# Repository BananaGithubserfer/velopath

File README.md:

# VeloPath

VeloPath is a multi-part cycling navigation project that combines a mobile application, embedded firmware, electronics design, and engineering documentation in one repository.

The repository contains:

- an Android application with map-based routing and BLE integration
- STM32 firmware for the handlebar module
- ESP-based firmware experiments and tools
- PCB design files and production artifacts
- project documentation, reports, and presentation materials

## Project Overview

VeloPath is organized as a single workspace for both software and hardware development. The Android app is responsible for route search, map display, navigation flow, and communication with the handlebar device. The embedded side includes STM32 firmware for the main hardware module and a separate ESP area for related experiments and peripherals.

At the application level, the current Android project includes:

- destination search and map interaction
- route building and route analytics
- BLE device diagnostics
- handlebar communication for navigation cues
- user settings such as theme and rider speed

## Repository Structure

```text
velopath/
|- app/
|  `- velopath3_project/    Android app and canonical STM32 firmware
|- firmware/
|  `- esp/                  ESP code and isolated tools
|- pcb/                     KiCad projects and manufacturing outputs
|- documentation/           Reports, engineering docs, mechanical docs
|- advertising/             Brochures, presentations, visual assets
|- INDEX.md                 Detailed project map
`- START_HERE.md            Quick onboarding guide
```

## Main Components

### Android App

Path: `app/velopath3_project`

Stack:

- Kotlin
- Jetpack Compose
- Android Navigation Compose
- Yandex MapKit
- Google Play Services Location

The main navigation flow currently includes:

- `DashboardScreen` for search and quick route entry
- `RideMapScreen` for active route guidance and map view
- `DeviceDiagnosticsScreen` for BLE connection and device checks
- `SettingsScreen` for app preferences

### STM32 Firmware

Path: `app/velopath3_project/firmware`

This area contains firmware for the handlebar module based on `STM32F103RGTx`. The documented hardware integration includes:

- BLE UART bridge `WH-BLE106`
- compass `LIS3MDL`
- left and right vibration channels

The firmware tree includes CubeMX project files, startup code, drivers, linker scripts, and diagnostics tooling.

### ESP Area

Path: `firmware/esp`

This directory is the isolated zone for ESP-related source code and tools. Build output and temporary files are local-only and ignored.

### PCB and Electronics

Path: `pcb`

This directory contains KiCad schematics, PCB layouts, fabrication outputs, and related electronics assets.

### Documentation and Materials

Paths:

- `documentation`
- `advertising`

These directories hold project reports, engineering notes, explanatory materials, brochures, and visual assets.

## Quick Start

### 1. Explore the Repository

Start here if you are new to the project:

1. Open `START_HERE.md`
2. Read `INDEX.md`
3. Review `documentation/software_stack_non_esp.md`

### 2. Build the Android App

Run in `app/velopath3_project`:

```powershell
.\gradlew.bat :app:assembleDebug
```

Release build:

```powershell
.\gradlew.bat :app:assembleRelease
```

The Android project expects local configuration through standard Gradle local files in the project root.

### 3. Work with STM32 Firmware

Start in `app/velopath3_project/firmware` if you are working on the main handlebar firmware. Typical files include:

- `firmware.ioc`
- `Core/`
- `Drivers/`
- `Startup/`
- STM32 linker scripts

### 4. Work with ESP Firmware

For ESP tasks, use `firmware/esp`.

Example PlatformIO upload command from the ESP project root:

```powershell
python -m platformio run -t upload --upload-port COM5
```

## Important Project Documents

- `START_HERE.md` - onboarding order for new contributors
- `INDEX.md` - high-level project map
- `documentation/software_stack_non_esp.md` - software overview outside the ESP area
- `documentation/materials_origin_and_import_map.md` - repository placement and source mapping
- `documentation/software_stack_non_esp.md` - software overview and build boundaries

## Suggested Entry Points By Task

- Mobile app work: `app/velopath3_project`
- Main embedded firmware: `app/velopath3_project/firmware`
- ESP work: `firmware/esp`
- PCB and hardware files: `pcb`
- Reports and engineering docs: `documentation`
- Presentations and brochure assets: `advertising`

## Status

This repository contains the active product sources, hardware files, engineering documentation, and supporting production materials. Generated workspaces, logs, caches, backups, and local credentials are intentionally excluded.

## License

This repository is distributed under the GNU General Public License v3.0 or later. See `LICENSE`.

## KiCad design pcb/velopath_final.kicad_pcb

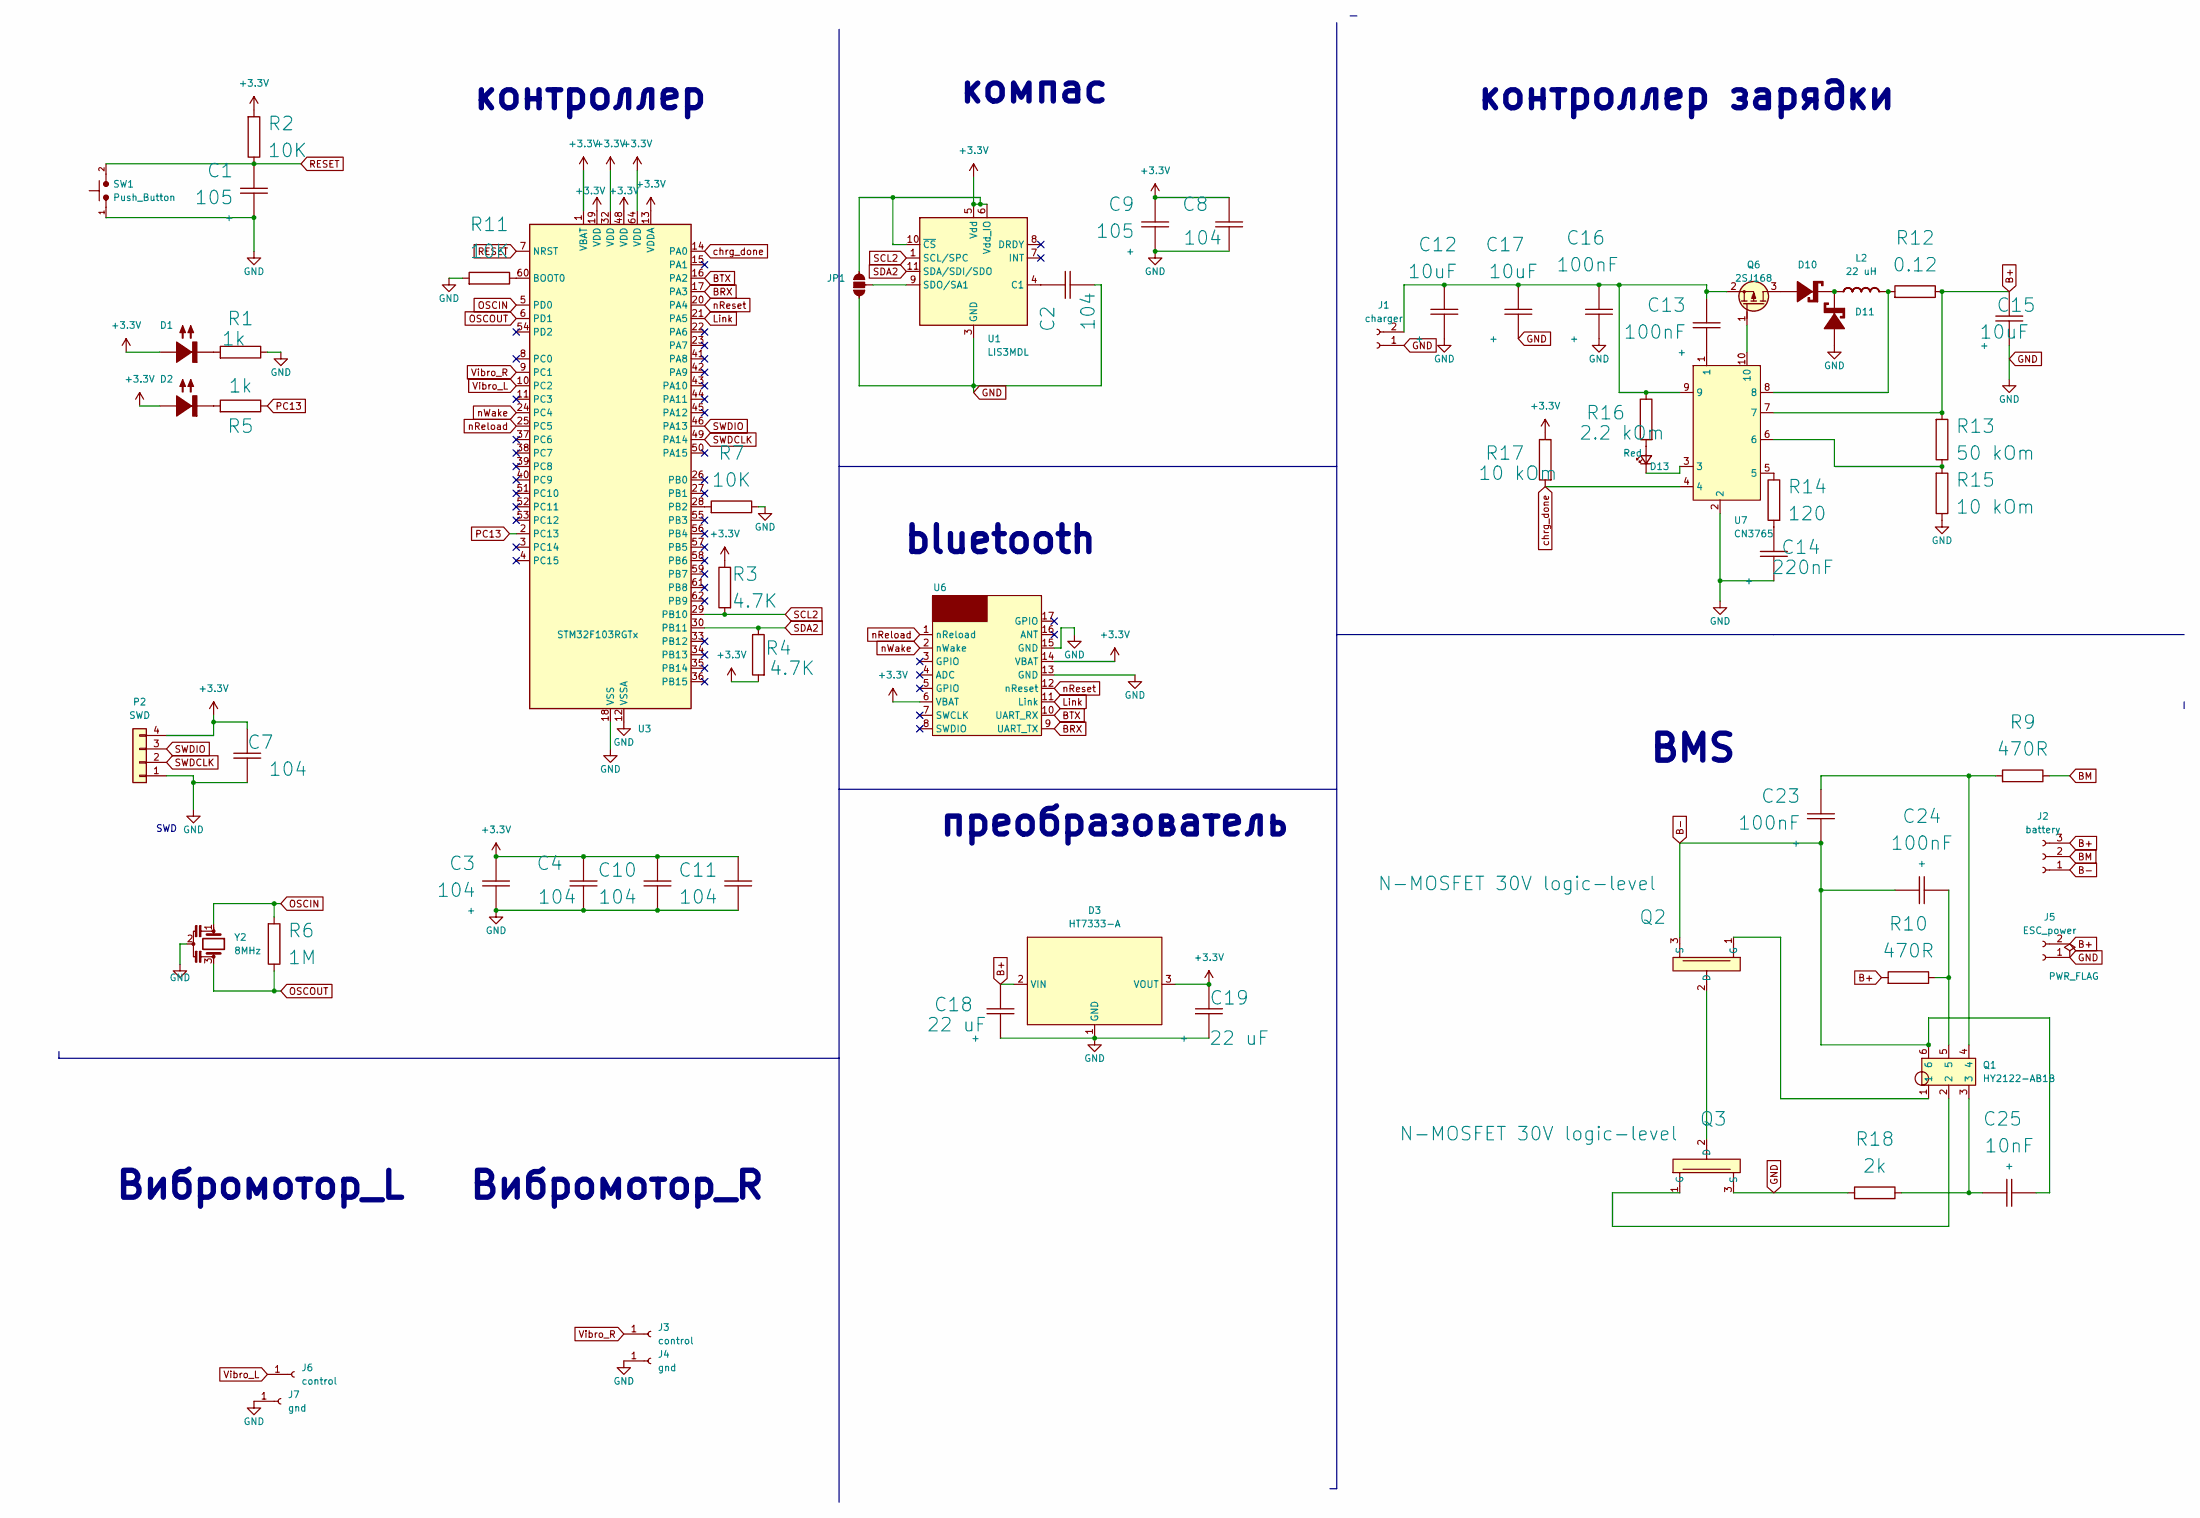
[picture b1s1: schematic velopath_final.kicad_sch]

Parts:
C1, C9: 105; C_0402_1005Metric_Pad0.74x0.62mm_HandSolder
C2, C3, C4, C7, C8, C10, C11: 104; C_0402_1005Metric_Pad0.74x0.62mm_HandSolder
C12, C15, C17: 10uF; C_0603_1608Metric_Pad1.05x0.95mm_HandSolder
C13, C16: 100nF; C_0402
C14: 220nF; C_0402
C18, C19: 22 uF; C_0402_1005Metric_Pad0.74x0.62mm_HandSolder
C23: 100nF; C_0603
C24: 100nF; C_0603_1608Metric_Pad1.08x0.95mm_HandSolder
C25: 10nF; C_0603_1608Metric_Pad1.08x0.95mm_HandSolder
D1, D2: LED_0603_1608Metric_Pad1.05x0.95mm_HandSolder; Rating A
D3: HT7333-A; SOT-89-3_Handsoldering
D10, D11: SOD-123; Rating V/A
D13: Red; LED_0603_1608Metric
J1: charger; Socket_1x02_2.54mm_TH
J2: battery; PinSocket_1x03_P2.54mm_Vertical
J3, J6: control; 1x01_P2.0mm
J4, J7: gnd; 1x01_P2.0mm
J5: ESC_power; Socket_1x02_2.54mm_TH
JP1: SolderJumper-3_P1.3mm_Open_Pad1.0x1.5mm
L2: 22 uH; L_Vishay_IHLP-2525; Rating A
P2: SWD; PinSocket_1x04_P2.00mm_Vertical; Part Number 1-0401FBV0T
Q1: HY2122-AB1B; TSOT-23-6
Q2, Q3: N-MOSFET 30V logic-level; TO-252-2
Q6: 2SJ168; SC-59
R1, R5: 1k; R_0402_1005Metric_Pad0.72x0.64mm_HandSolder
R2, R7, R11: 10K; R_0402_1005Metric_Pad0.72x0.64mm_HandSolder
R3, R4: 4.7K; R_0402_1005Metric_Pad0.72x0.64mm_HandSolder
R6: 1M; R_0402_1005Metric_Pad0.72x0.64mm_HandSolder
R9, R10: 470R; R_0603_1608Metric_Pad0.98x0.95mm_HandSolder
R12: 0.12; R_0402
R13: 50 kOm; R_0402
R14: 120; R_0402
R15: 10 kOm; R_0402
R16: 2.2 kOm; R_0402
R17: 10 kOm; R_0402_1005Metric_Pad0.72x0.64mm_HandSolder
R18: 2k; R_0603_1608Metric_Pad0.98x0.95mm_HandSolder
SW1: Push_Button; SW_SPST_PTS810
U1: LIS3MDL; LGA-12_2x2mm_P0.5mm
U3: STM32F103RGTx; LQFP-64_10x10mm_P0.5mm
U6: WH-BLE106
U7: CN3765; SSOP-10_3.9x4.9mm_P1.00mm
Y2: 8MHz; Resonator_SMD_Murata_CSTxExxV-3Pin_3.0x1.1mm_HandSoldering

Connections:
+3.3V: C3.1 (+), C4.1 (+), C7.1 (+), C8.1 (+), C9.1 (+), C10.1 (+), C11.1 (+), C19.1 (+), D1.2 (A+), D2.2 (A+), D3.3 (VOUT), JP1.3 (C), P2.4, R2.1 (+), R3.2 (-), R4.1 (+), R17.2 (-), U1.5 (Vdd), U1.6 (Vdd_IO), U1.10 (~CS), U3.1 (VBAT), U3.13 (VDDA), U3.19 (VDD), U3.32 (VDD), U3.48 (VDD), U3.64 (VDD), U6.6 (VBAT), U6.14 (VBAT)
B+: C15.1 (+), C18.1 (+), D3.2 (VIN), J2.3, J5.2, R10.1 (+), R12.2 (-), R13.1 (+), U7.7
B-: C23.1 (+), C24.1 (+), C25.2 (-), J2.1, Q1.6, Q2.3 (S)
BM: J2.2, R9.2 (-)
BRX: U3.17 (PA3), U6.9 (UART_TX)
BTX: U3.16 (PA2), U6.10 (UART_RX)
GND: C1.2 (-), C2.2 (-), C3.2 (-), C4.2 (-), C7.2 (-), C8.2 (-), C9.2 (-), C10.2 (-), C11.2 (-), C12.2 (-), C14.1 (+), C15.2 (-), C16.2 (-), C17.2 (-), C18.2 (-), C19.2 (-), D3.1 (GND), D11.2 (A+), J1.1, J4.1 (Pin_1_1), J5.1, J7.1 (Pin_1_1), JP1.1 (A), P2.1, Q3.3 (S), R1.2 (-), R7.2 (-), R11.1 (+), R15.2 (-), R18.1 (+), SW1.1, U1.2 (GND), U1.3 (GND), U1.12 (GND), U3.12 (VSSA), U3.18 (VSS), U3.31 (VSS), U3.47 (VSS), U3.63 (VSS), U6.13 (GND), U6.15 (GND), U7.2, Y2.2
Link: U3.21 (PA5), U6.11 (Link)
unnamed: C2.1 (+), U1.4 (C1)
unnamed: C12.1 (+), C13.1 (+), C16.1 (+), C17.1 (+), J1.2, Q6.2 (S), R16.2 (-), U7.9
unnamed: C13.2 (-), U7.1
unnamed: C14.2 (-), R14.1 (+)
unnamed: C23.2 (-), Q1.4, R9.1 (+)
unnamed: C24.2 (-), Q1.5, R10.2 (-)
unnamed: C25.1 (+), Q1.3, R18.2 (-)
unnamed: D1.1 (K-), R1.1 (+)
unnamed: D2.1 (K-), R5.1 (+)
unnamed: D10.2 (A+), Q6.3 (D)
unnamed: D10.1 (K-), D11.1 (K-), L2.1 (+)
unnamed: D13.2 (A), R16.1 (+)
unnamed: D13.1 (K), U7.3
unnamed: JP1.2 (B), U1.9 (SDO/SA1)
unnamed: L2.2 (-), R12.1 (+), U7.8
unnamed: Q2.2 (D), Q3.2 (D)
unnamed: Q1.1, Q2.1 (G)
unnamed: Q1.2, Q3.1 (G)
unnamed: Q6.1 (G), U7.10
unnamed: R7.1 (+), U3.28 (PB2)
unnamed: R11.2 (-), U3.60 (BOOT0)
unnamed: R13.2 (-), R15.1 (+), U7.6
unnamed: R14.2 (-), U7.5
OSCIN: R6.1 (+), U3.5 (PD0), Y2.1
OSCOUT: R6.2 (-), U3.6 (PD1), Y2.3
PC13: R5.2 (-), U3.2 (PC13)
RESET: C1.1 (+), R2.2 (-), SW1.2, U3.7 (NRST)
SCL2: R3.1 (+), U1.1 (SCL/SPC), U3.29 (PB10)
SDA2: R4.2 (-), U1.11 (SDA/SDI/SDO), U3.30 (PB11)
SWDCLK: P2.2, U3.49 (PA14)
SWDIO: P2.3, U3.46 (PA13)
Vibro_L: J6.1 (Pin_1_1), U3.10 (PC2)
Vibro_R: J3.1 (Pin_1_1), U3.9 (PC1)
chrg_done: R17.1 (+), U3.14 (PA0), U7.4
nReload: U3.25 (PC5), U6.1 (nReload)
nReset: U3.20 (PA4), U6.12 (nReset)
nWake: U3.24 (PC4), U6.2 (nWake)

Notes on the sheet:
Вибромотор_R
bluetooth
контроллер зарядки
преобразователь
SWD
контроллер
компас
BMS
Вибромотор_L

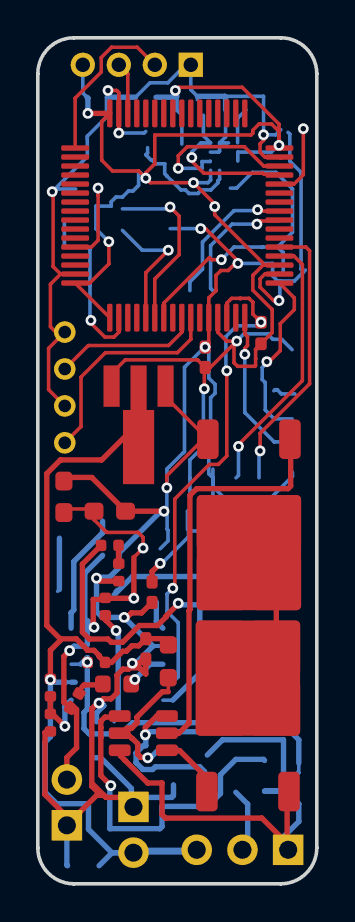
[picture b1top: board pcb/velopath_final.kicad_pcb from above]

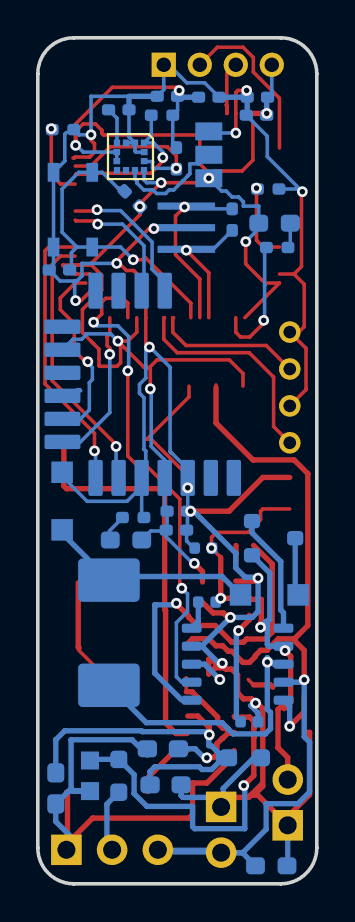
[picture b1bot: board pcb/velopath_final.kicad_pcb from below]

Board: 2 copper layers, 15.5 x 47.0 mm, 63 parts (36 on the bottom side), 45 nets.

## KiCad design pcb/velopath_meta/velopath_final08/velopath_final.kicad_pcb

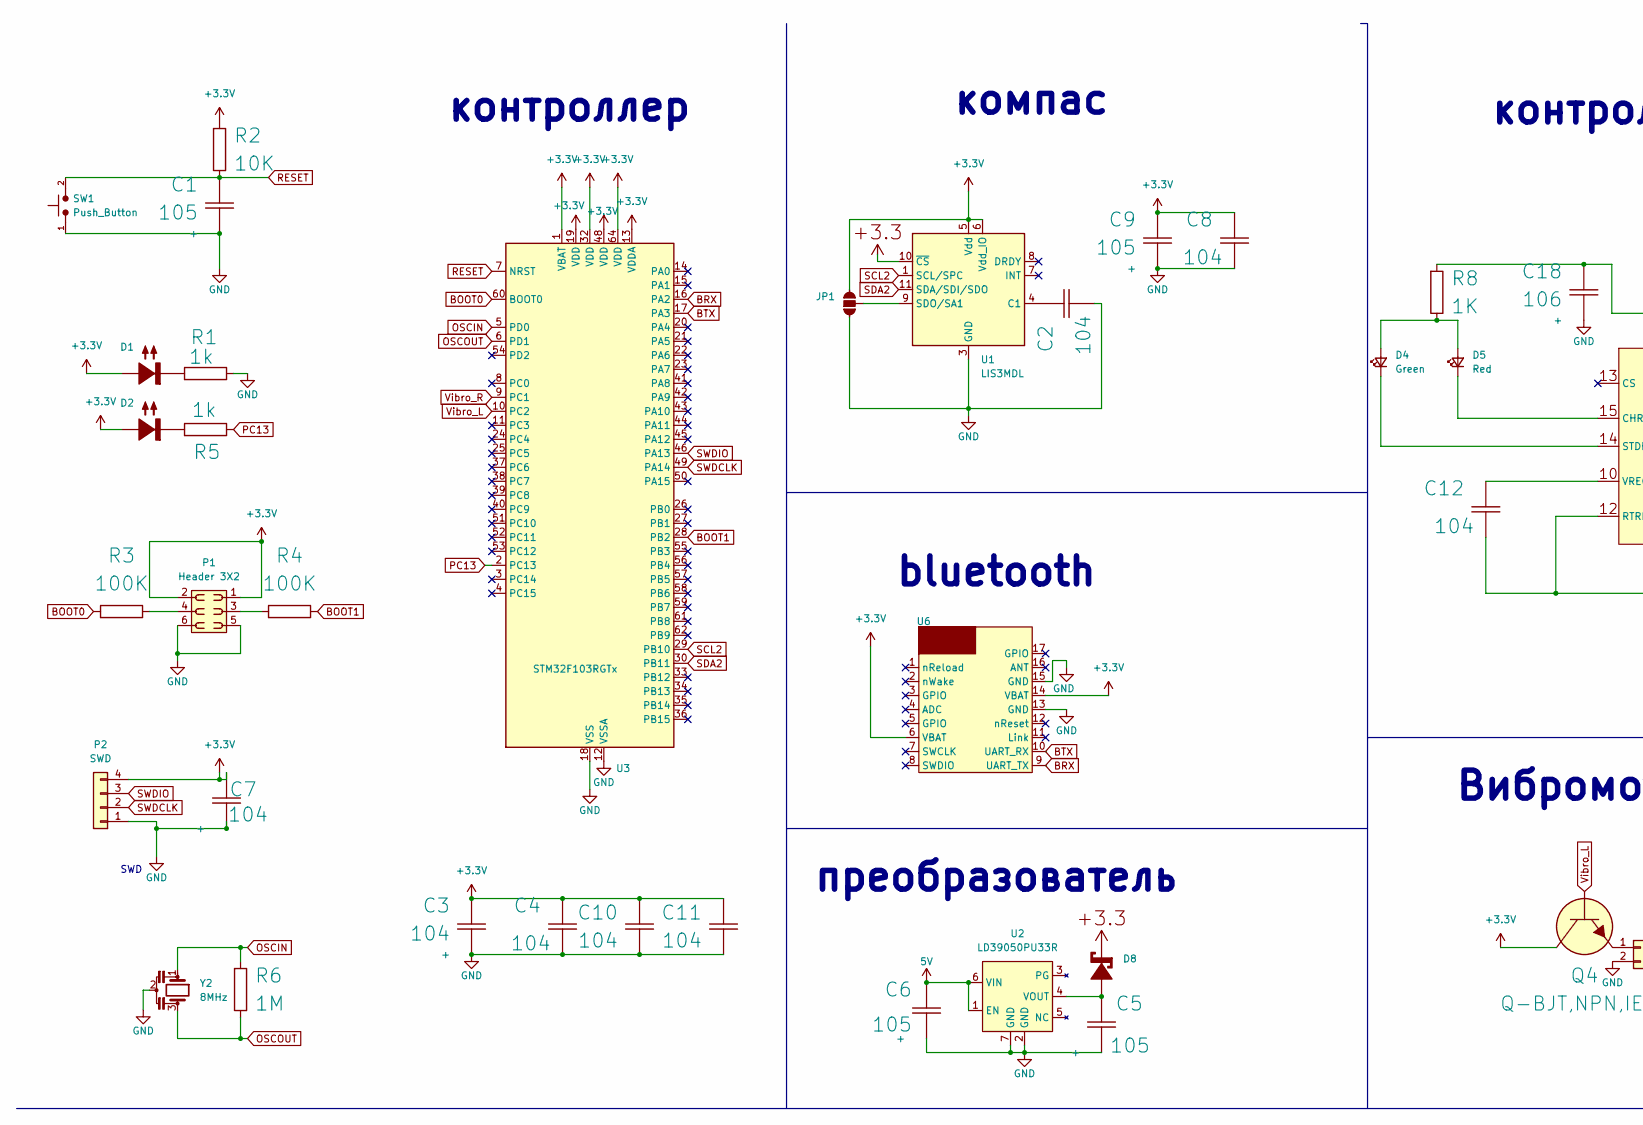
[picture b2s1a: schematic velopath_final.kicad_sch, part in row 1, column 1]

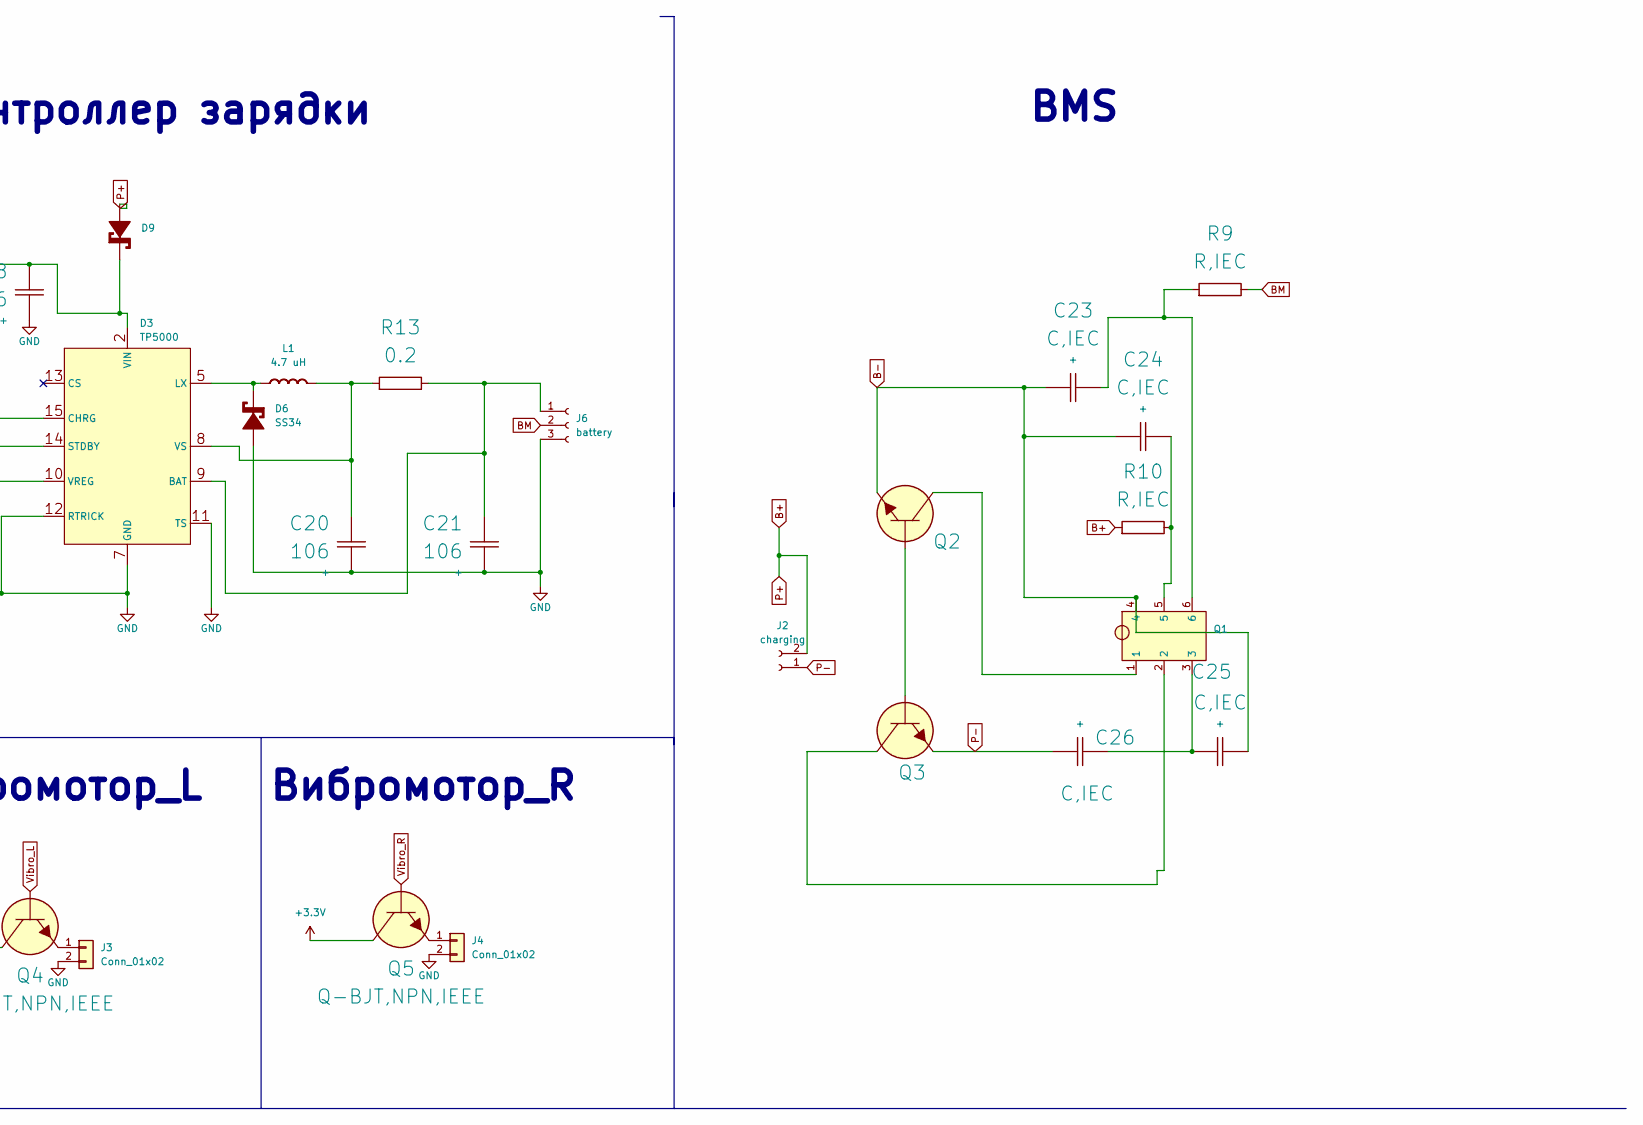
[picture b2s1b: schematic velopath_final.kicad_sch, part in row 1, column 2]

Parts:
C1, C5, C6, C9: 105; C_0402_1005Metric_Pad0.74x0.62mm_HandSolder
C2, C3, C4, C7, C8, C10, C11, C12: 104; C_0402_1005Metric_Pad0.74x0.62mm_HandSolder
C18, C20, C21: 106; C_0402_1005Metric_Pad0.74x0.62mm_HandSolder
C23, C24, C25, C26: C,IEC; C_0603_1608Metric_Pad1.08x0.95mm_HandSolder
D1, D2: LED_0603_1608Metric_Pad1.05x0.95mm_HandSolder; Rating A
D3: TP5000; QFN-16-1EP_4x4mm_P0.65mm_EP2.5x2.5mm
D4: Green; LED_0603_1608Metric_Pad1.05x0.95mm_HandSolder
D5: Red; LED_0603_1608Metric_Pad1.05x0.95mm_HandSolder
D6: SS34; D_SMA_Handsoldering; Rating V/A
D8, D9: D_SOD-123; Rating V/A
J2: charging; PinSocket_1x02_P2.00mm_Vertical
J3, J4: Conn_01x02; PinSocket_1x02_P2.00mm_Vertical; Part Number 1-0201FBV0T
J6: battery; PinSocket_1x03_P2.00mm_Vertical
JP1: SolderJumper-3_P1.3mm_Open_Pad1.0x1.5mm
L1: 4.7 uH; L_Vishay_IHLP-2525; Rating A
P1: Header 3X2; PinSocket_2x03_P2.00mm_Vertical
P2: SWD; PinSocket_1x04_P2.00mm_Vertical; Part Number 1-0401FBV0T
Q1: SOT-23-6
Q2, Q3: TO-252-2
Q4, Q5: Q-BJT,NPN,IEEE; SOT-23
R1, R5: 1k; R_0402_1005Metric_Pad0.72x0.64mm_HandSolder
R2: 10K; R_0402_1005Metric_Pad0.72x0.64mm_HandSolder
R3, R4: 100K; R_0402_1005Metric_Pad0.72x0.64mm_HandSolder
R6: 1M; R_0402_1005Metric_Pad0.72x0.64mm_HandSolder
R8: 1K; R_0402_1005Metric_Pad0.72x0.64mm_HandSolder
R9, R10: R,IEC; R_0603_1608Metric_Pad0.98x0.95mm_HandSolder
R13: 0.2; R_0603_1608Metric_Pad0.98x0.95mm_HandSolder
SW1: Push_Button; SW_SPST_PTS810
U1: LIS3MDL; LGA-12_2x2mm_P0.5mm
U2: LD39050PU33R; DFN-6-1EP_3x3mm_P0.95mm_EP1.7x2.6mm
U3: STM32F103RGTx; LQFP-64_10x10mm_P0.5mm
U6: WH-BLE106
Y2: 8MHz; Resonator_SMD_Murata_CSTxExxV-3Pin_3.0x1.1mm_HandSoldering

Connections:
5V: C6.1 (+), U2.1 (EN), U2.6 (VIN)
+3.3V: C3.1 (+), C4.1 (+), C7.1 (+), C8.1 (+), C9.1 (+), C10.1 (+), C11.1 (+), D1.2 (A+), D2.2 (A+), JP1.3 (C), P1.1, P1.2, P2.4, Q4.1 (C), Q5.1 (C), R2.1 (+), U1.5 (Vdd), U1.6 (Vdd_IO), U3.1 (VBAT), U3.13 (VDDA), U3.19 (VDD), U3.32 (VDD), U3.48 (VDD), U3.64 (VDD), U6.6 (VBAT), U6.14 (VBAT)
B+: D9.2 (A+), J2.2, R10.1 (+)
B-: C23.1 (+), C24.1 (+), C25.2 (-), Q1.4, Q2.3 (E)
BM: J6.2, R9.2 (-)
BOOT0: R3.1 (+), U3.60 (BOOT0)
BOOT1: R4.2 (-), U3.28 (PB2)
BRX: U3.16 (PA2), U6.9 (UART_TX)
BTX: U3.17 (PA3), U6.10 (UART_RX)
GND: C1.2 (-), C2.2 (-), C3.2 (-), C4.2 (-), C5.2 (-), C6.2 (-), C7.2 (-), C8.2 (-), C9.2 (-), C10.2 (-), C11.2 (-), C12.2 (-), C18.2 (-), C20.2 (-), C21.2 (-), D3.6 (GND), D3.7 (GND), D3.11 (TS), D3.12 (RTRICK), D6.2 (A+), J3.2, J4.2, J6.3, JP1.1 (A), P1.5, P1.6, P2.1, R1.2 (-), SW1.1, U1.2 (GND), U1.3 (GND), U1.12 (GND), U2.2 (GND), U2.7 (GND), U3.12 (VSSA), U3.18 (VSS), U3.31 (VSS), U3.47 (VSS), U3.63 (VSS), U6.13 (GND), U6.15 (GND), Y2.2
unnamed: C2.1 (+), U1.4 (C1)
unnamed: C5.1 (+), D8.2 (A+), U2.4 (VOUT)
unnamed: C12.1 (+), D3.10 (VREG)
unnamed: C18.1 (+), D3.1 (VIN), D3.2 (VIN), D3.16 (VIN), D9.1 (K-), R8.1 (+)
unnamed: C20.1 (+), D3.8 (VS), L1.2 (-), R13.1 (+)
unnamed: C21.1 (+), D3.9 (BAT), J6.1, R13.2 (-)
unnamed: C23.2 (-), Q1.6, R9.1 (+)
unnamed: C24.2 (-), Q1.5, R10.2 (-)
unnamed: C25.1 (+), C26.2 (-), Q1.3
unnamed: D1.1 (K-), R1.1 (+)
unnamed: D2.1 (K-), R5.1 (+)
unnamed: D3.15 (CHRG), D5.1 (K)
unnamed: D3.14 (STDBY), D4.1 (K)
unnamed: D4.2 (A), D5.2 (A), R8.2 (-)
unnamed: D3.3 (LX), D3.4 (LX), D3.5 (LX), D6.1 (K-), L1.1 (+)
unnamed: J3.1, Q4.3 (E)
unnamed: J4.1, Q5.3 (E)
unnamed: JP1.2 (B), U1.9 (SDO/SA1)
unnamed: Q2.2 (B), Q3.2 (B)
unnamed: Q1.1, Q2.1 (C)
unnamed: Q1.2, Q3.1 (C)
unnamed: P1.4, R3.2 (-)
unnamed: P1.3, R4.1 (+)
OSCIN: R6.1 (+), U3.5 (PD0), Y2.1
OSCOUT: R6.2 (-), U3.6 (PD1), Y2.3
P,+3.3: D8.1 (K-), U1.10 (~CS)
P-: C26.1 (+), J2.1, Q3.3 (E)
PC13: R5.2 (-), U3.2 (PC13)
RESET: C1.1 (+), R2.2 (-), SW1.2, U3.7 (NRST)
SCL2: U1.1 (SCL/SPC), U3.29 (PB10)
SDA2: U1.11 (SDA/SDI/SDO), U3.30 (PB11)
SWDCLK: P2.2, U3.49 (PA14)
SWDIO: P2.3, U3.46 (PA13)
Vibro_L: Q4.2 (B), U3.10 (PC2)
Vibro_R: Q5.2 (B), U3.9 (PC1)

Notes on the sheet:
bluetooth
контроллер зарядки
преобразователь
Вибромотор_L
SWD
контроллер
компас
BMS
Вибромотор_R

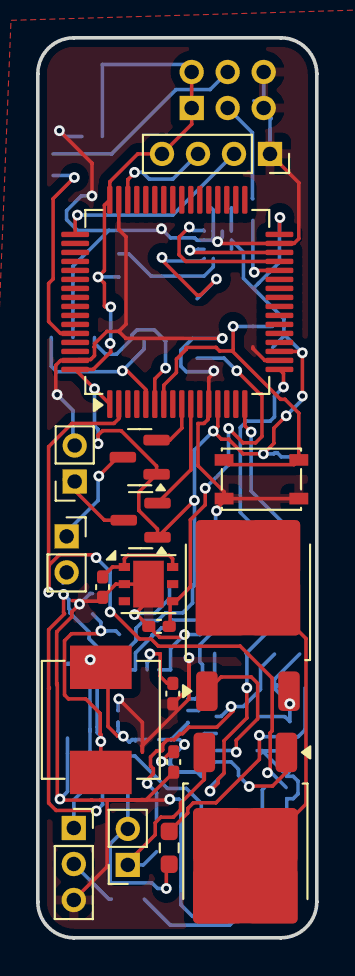
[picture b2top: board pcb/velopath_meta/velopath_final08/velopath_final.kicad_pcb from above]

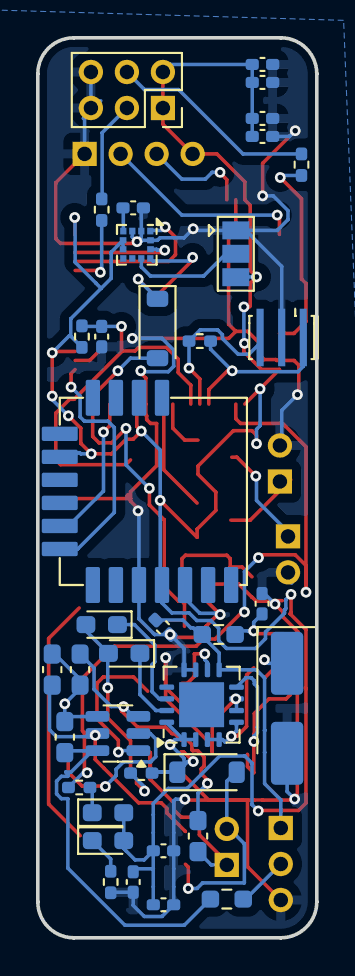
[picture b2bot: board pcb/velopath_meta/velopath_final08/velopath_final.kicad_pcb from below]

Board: 2 copper layers, 15.5 x 50.0 mm, 56 parts (38 on the bottom side), 45 nets.

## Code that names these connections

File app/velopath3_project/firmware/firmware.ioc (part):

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Mcu.Name=STM32F103R(F-G)Tx
Mcu.Package=LQFP64
Mcu.UserName=STM32F103RGTx
PA13.Mode=Serial_Wire
PA13.Signal=SYS_JTMS-SWDIO
PA14.Mode=Serial_Wire
PA14.Signal=SYS_JTCK-SWCLK
PA2.Mode=Asynchronous
PA2.Signal=USART2_TX
PA3.Mode=Asynchronous
PA3.Signal=USART2_RX
PB10.Mode=I2C
PB10.Signal=I2C2_SCL
PB11.Mode=I2C
PB11.Signal=I2C2_SDA
PC1.GPIOParameters=GPIO_Label
PC1.GPIO_Label=LEFT_MOTOR
PC1.Signal=GPIO_Output
PC2.GPIOParameters=GPIO_Label
PC2.GPIO_Label=RIGHT_MOTOR
PC2.Signal=GPIO_Output
PD0-OSC_IN.Mode=HSE-External-Oscillator
PD0-OSC_IN.Signal=RCC_OSC_IN
PD1-OSC_OUT.Mode=HSE-External-Oscillator
PD1-OSC_OUT.Signal=RCC_OSC_OUT
RCC.SYSCLKFreq_VALUE=72000000
RCC.SYSCLKSource=RCC_SYSCLKSOURCE_PLLCLK
board=custom
